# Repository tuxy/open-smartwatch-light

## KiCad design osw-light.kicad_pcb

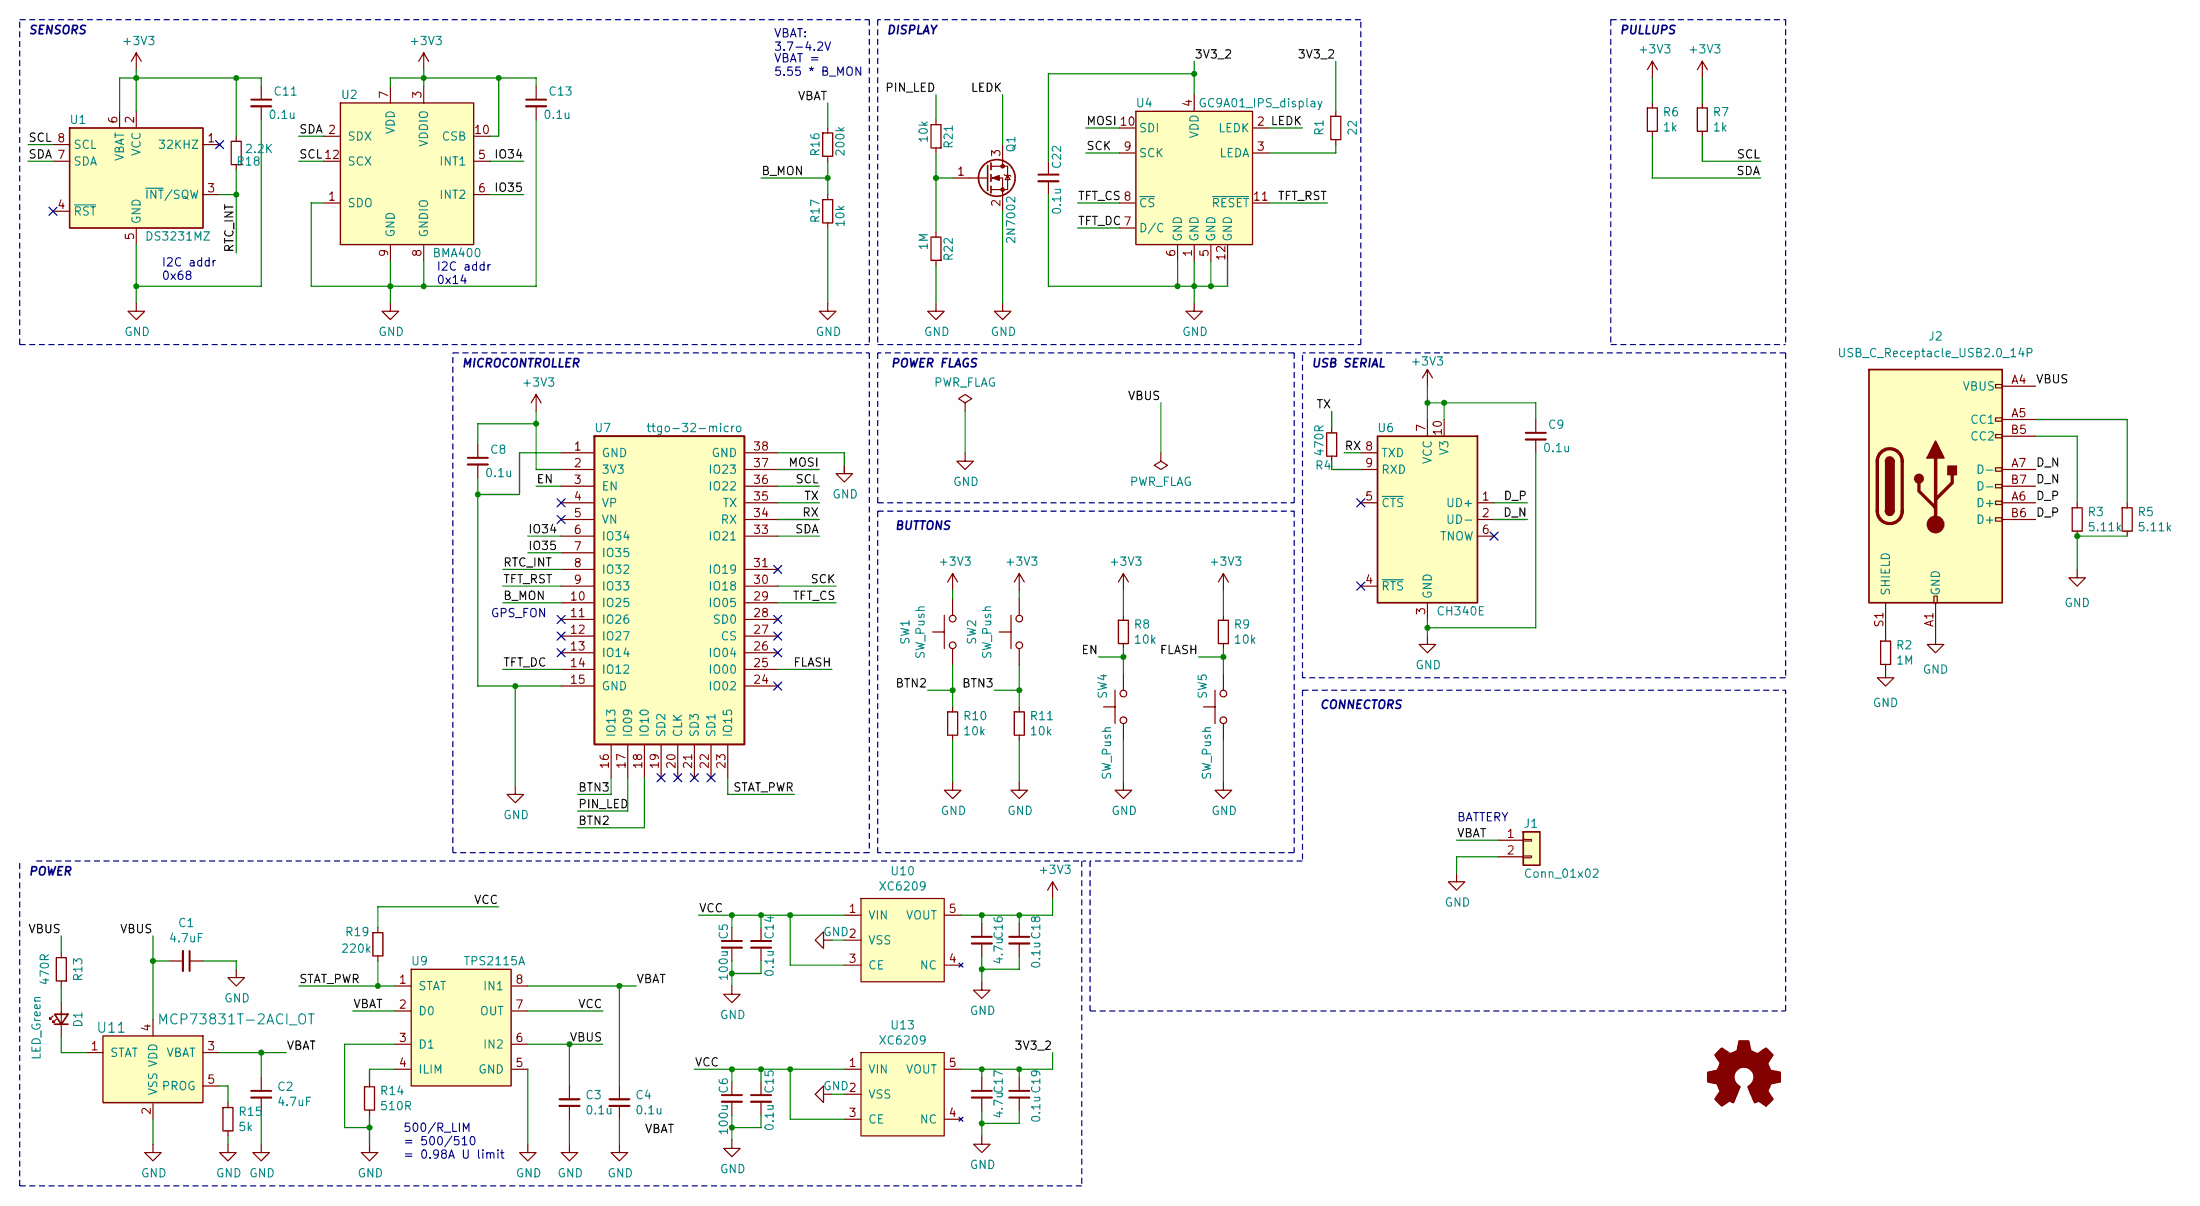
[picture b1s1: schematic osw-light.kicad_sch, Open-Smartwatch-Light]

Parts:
C1, C2: 4.7uF; C_0603_1608Metric
C3, C4, C8, C9, C11, C13, C14, C15, C18, C19, C22: 0.1u; C_0603_1608Metric
C5, C6: 100u; C_1206_3216Metric
C16, C17: 4.7u; C_0603_1608Metric
D1: LED_Green; LED_0805_2012Metric
J1: Conn_01x02; PinHeader_1x02_P2.54mm_Vertical
J2: USB_C_Receptacle_USB2.0_14P; USB_C_Receptacle_JAE_DX07S016JA1R1500
Q1: 2N7002; SOT-23
R1: 22; R_0603_1608Metric
R2, R22: 1M; R_0603_1608Metric
R3, R5: 5.11k; R_0603_1608Metric
R4, R13: 470R; R_0603_1608Metric
R6, R7: 1k; R_0603_1608Metric
R8, R9, R10, R11, R17, R21: 10k; R_0603_1608Metric
R14: 510R; R_0603_1608Metric
R15: 5k; R_0603_1608Metric
R16: 200k; R_0603_1608Metric
R18: 2.2K; R_0603_1608Metric
R19: 220k; R_0603_1608Metric
SW1, SW2, SW4, SW5: SW_Push; button_side_smd
U1: DS3231MZ; SOIC-8_3.9x4.9mm_P1.27mm
U2: BMA400; LGA-12_2x2mm_P0.5mm; MPN BMA400; DigiKey_PN 828-1081-1-ND
U4: GC9A01_IPS_display
U6: CH340E; MSOP-10_3x3mm_P0.5mm
U7: ttgo-32-micro
U9: TPS2115A; TSSOP-8_4.4x3mm_P0.65mm; MPN TPS2115APWR; DigiKey_PN 296-16940-1-ND
U10, U13: XC6209; SOT-23-5
U11: MCP73831T-2ACI_OT; SOT-23-5; MPN MCP73831T-2ACI/OT; Digi-Key_PN MCP73831T-2ACI/OTCT-ND

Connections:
+3V3: C8.1, C9.1, C11.1, C13.1, C16.1, C18.1, R6.1, R7.1, R8.1, R9.1, R18.2, SW1.2, SW2.2, U1.2 (VCC), U1.6 (VBAT), U2.3 (VDDIO), U2.7 (VDD), U2.10 (CSB), U6.7 (VCC), U6.10 (V3), U7.2 (3V3), U10.5 (VOUT)
/3V3_2: C17.1, C19.1, C22.1, R1.1, U4.4 (VDD), U13.5 (VOUT)
/BTN2: R10.1, SW1.1, U7.18 (IO10)
/BTN3: R11.1, SW2.1, U7.16 (IO13)
/B_MON: R16.2, R17.1, U7.10 (IO25)
/D_N: J2.A7 (D-), J2.B7 (D-), U6.2 (UD-)
/D_P: J2.A6 (D+), J2.B6 (D+), U6.1 (UD+)
/EN: R8.2, SW4.2, U7.3 (EN)
/FLASH: R9.2, SW5.2, U7.25 (IO00)
/IO34: U2.5 (INT1), U7.6 (IO34)
/IO35: U2.6 (INT2), U7.7 (IO35)
/LEDK: Q1.3 (D), U4.2 (LEDK)
/MOSI: U4.10 (SDI), U7.37 (IO23)
/PIN_LED: R21.2, U7.17 (IO09)
/RTC_INT: R18.1, U1.3 (~INT/SQW), U7.8 (IO32)
/RX: U6.8 (TXD), U7.34 (RX)
/SCK: U4.9 (SCK), U7.30 (IO18)
/SCL: R7.2, U1.8 (SCL), U2.12 (SCX), U7.36 (IO22)
/SDA: R6.2, U1.7 (SDA), U2.2 (SDX), U7.33 (IO21)
/STAT_PWR: R19.2, U7.23 (IO15), U9.1 (STAT)
/TFT_CS: U4.8 (~CS), U7.29 (IO05)
/TFT_DC: U4.7 (D/C), U7.14 (IO12)
/TFT_RST: U4.11 (~RESET), U7.9 (IO33)
/TX: R4.2, U7.35 (TX)
/VBAT: C2.1, C4.1, J1.1, R16.1, U9.2 (D0), U9.8 (IN1), U11.3 (VBAT)
/VBUS: C1.2, C3.1, J2.A4 (VBUS), J2.A9 (VBUS), J2.B4 (VBUS), J2.B9 (VBUS), R13.2, U9.6 (IN2), U11.4 (VDD)
/VCC: C5.1, C6.1, C14.1, C15.1, R19.1, U9.7 (OUT), U10.1 (VIN), U10.3 (CE), U13.1 (VIN), U13.3 (CE)
GND: C1.1, C2.2, C3.2, C4.2, C5.2, C6.2, C8.2, C9.2, C11.2, C13.2, C14.2, C15.2, C16.2, C17.2, C18.2, C19.2, C22.2, J1.2, J2.A1 (GND), J2.A12 (GND), J2.B1 (GND), J2.B12 (GND), Q1.2 (S), R2.2, R3.2, R5.2, R10.2, R11.2, R14.2, R15.2, R17.2, R22.1, SW4.1, SW5.1, U1.5 (GND), U2.1 (SDO), U2.8 (GNDIO), U2.9 (GND), U4.1 (GND), U4.5 (GND), U4.6 (GND), U4.12 (GND), U6.3 (GND), U7.1 (GND), U7.15 (GND), U7.38 (GND), U9.3 (D1), U9.5 (GND), U10.2 (VSS), U11.2 (VSS), U13.2 (VSS)
unnamed: D1.2 (A), R13.1
unnamed: D1.1 (K), U11.1 (STAT)
unnamed: J2.A5 (CC1), R5.1
unnamed: J2.B5 (CC2), R3.1
unnamed: J2.S1 (SHIELD), R2.1
unnamed: Q1.1 (G), R21.1, R22.2
unnamed: R1.2, U4.3 (LEDA)
unnamed: R4.1, U6.9 (RXD)
unnamed: R14.1, U9.4 (ILIM)
unnamed: R15.1, U11.5 (PROG)

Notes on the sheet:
USB SERIAL
MICROCONTROLLER
DISPLAY
GPS_FON
I2C addr 0x68
VBAT = 5.55 * B_MON
500/R_LIM = 500/510 = 0.98A U limit
BATTERY
VBAT: 3.7-4.2V
POWER FLAGS
SENSORS
BUTTONS
CONNECTORS
I2C addr 0x14
PULLUPS
POWER

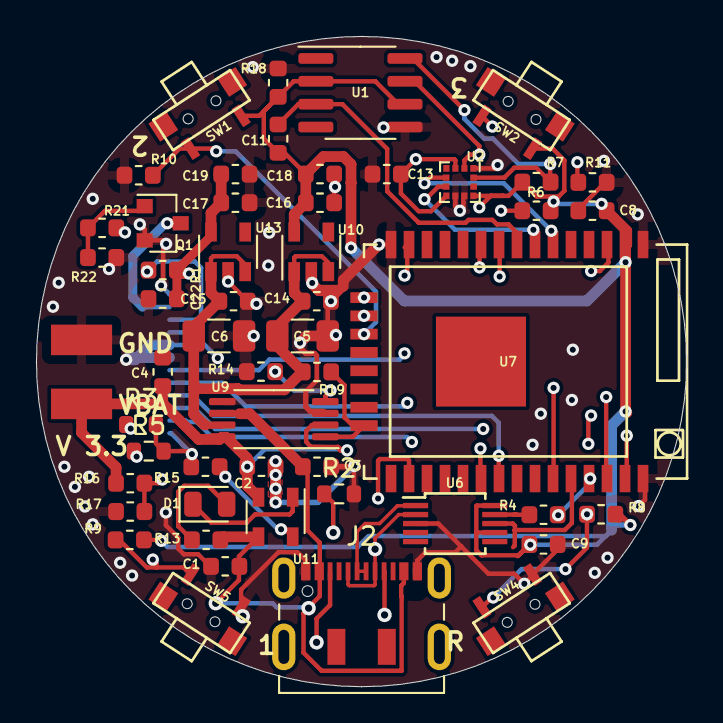
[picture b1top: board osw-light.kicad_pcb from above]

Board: 4 copper layers, 36.1 x 36.1 mm, 54 parts (1 on the bottom side), 38 nets.

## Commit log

2025-02-17 Added type c
